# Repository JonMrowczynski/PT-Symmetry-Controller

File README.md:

# PT-Symmetry-Controller

PT-Symmetric Quantum Theory is a non-Hermitian area of physics whose study has relatively recently gained a significant amount of popularity. The interplay between energy additions and subtractions to and from a system can lead to features that present new and interesting research topics.

This mechanical PT-Symmetry-Controller project is an analog to a quantum mechanical PT-symmetric system. It consists of two pendulums that are energetically coupled by a string that connects their pivot points. The amount of energy that can be transferred between the pendulums is determined by the tautness of the coupling string.

One of these pendulums has energy added to its swing while the other pendulum has energy subtracted from its swing. This is done by pulsing the pendulum's corresponding solenoid at specific times such that a magnet, which is attached to the string of each pendulum, has a force exerted on it. The driven pendulum has its corresponding solenoid pulsed when it is swinging towards its solenoid, while the dampened pendulum has its corresponding solenoid pulsed when it is swinging away from its solenoid.

Each pendulum has a photogate that assists with determining its swing direction. Each photogate is placed slightly offset from the resting position of the corresponding pendulum. This allows for two asymmetrical partial periods to be determined. This information is then used by the computer to determine when to pulse the corresponding solenoid. The two photogates interface with a LabQuest 2, which needs to be connected to the computer that is running the program.

Finally, a custom circuit is used to help pulse the solenoids. The computer program communicates with a microcontroller using a USB to MIDI connection. Based on the MIDI message that is sent to the microcontroller, and with the help of high amperage transistors, current can be sent to and cut off from each corresponding solenoid.

With this equipment, one can setup either a broken (insufficient coupling), or an unbroken (sufficient coupling) PT-symmetric mechanical system.

## Requirements for...

### Electronics

- Any PDF reader to view the PDF of the schematic.

- [Autodesk Eagle](https://www.autodesk.com/products/eagle/free-download) >= 9.5 to modify the schematic, board layout, and/or Gerber files.

### Firmware

#### Software

- [MPLAB X IDE](https://www.microchip.com/mplab/mplab-x-ide) >= 5.25 to modify and develop the firmware.

- MPLAB X IPE >= 5.25 to program the PIC microcontrollers.

  - While installing the IDE, you are presented with the choice of also installed the IPE.
  
  - The versions of MPLAB X IDE and MPLAB X IPE should be the same.
  
#### Hardware

- [PICkit 4 In-Circuit Debugger/Programmer](https://www.microchip.com/developmenttools/ProductDetails/PG164140) to flash the PIC microcontrollers with new firmware.

### LabQuest 2 Software

- [Microsoft Visual Studio IDE](https://visualstudio.microsoft.com/) >= 2019

Using the Visual Studio Installer that comes with the IDE install the "Desktop development with C++" workload:
  
#### Hardware

- [LabQuest 2](https://www.vernier.com/products/interfaces/labq2/)

- 2 [Vernier Photogates](https://www.vernier.com/products/sensors/photogates/vpg-btd/)

### Master Control Software

#### Software

- Both [OpenJDK](https://adoptopenjdk.net/) and [OpenJFX](https://gluonhq.com/products/javafx/) >= 11 to run and develop the software.
  - The versions of OpenJDK and OpenJFX should be the same.
  
- [Intellij IDEA](https://www.jetbrains.com/idea/download/) >= 2019.2 (recommended, but not necessary).

#### Hardware 

- [USB to MIDI cable](https://www.amazon.com/HDE-Synthesizer-Microphone-Instrument-Converter/dp/B00D3QFHN8/)

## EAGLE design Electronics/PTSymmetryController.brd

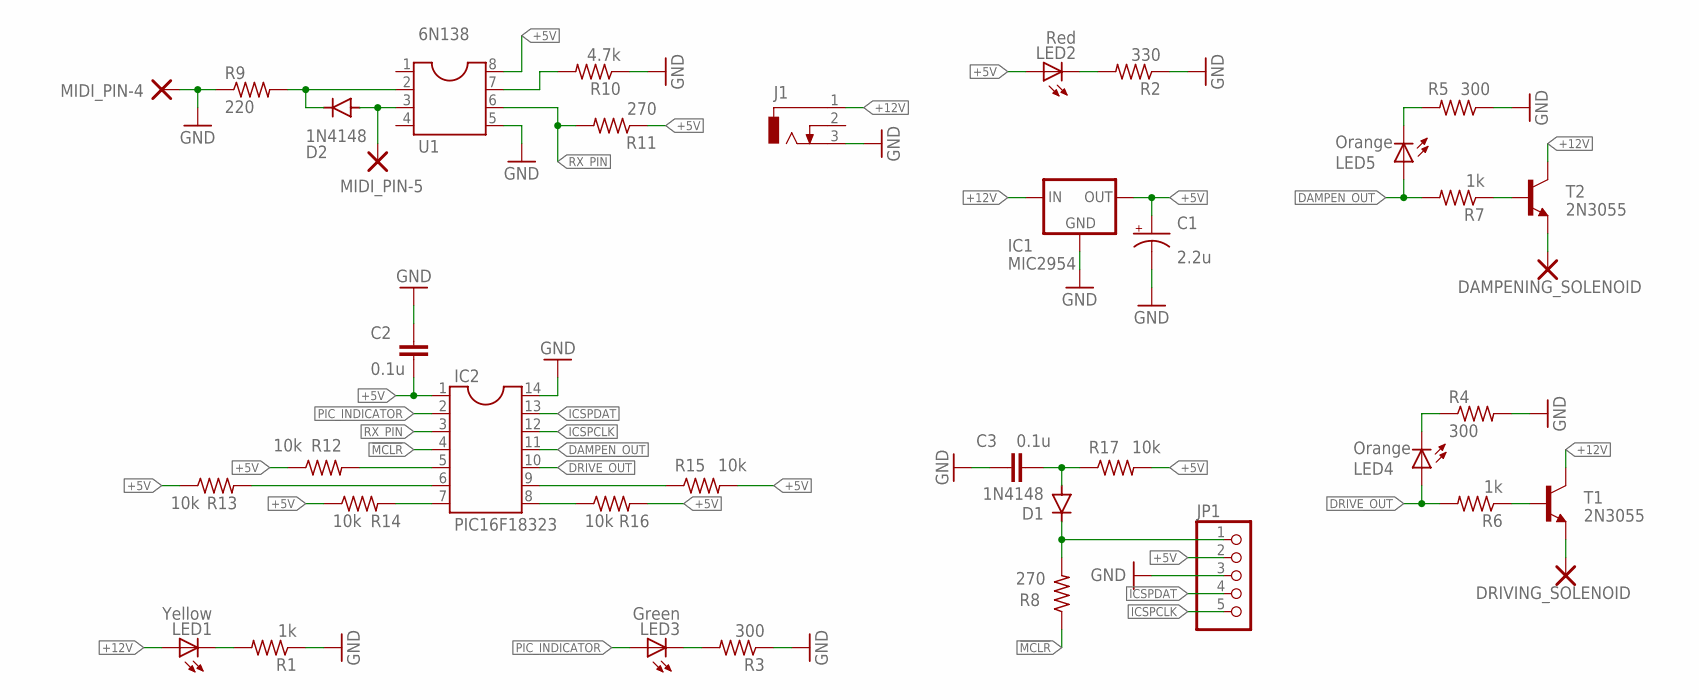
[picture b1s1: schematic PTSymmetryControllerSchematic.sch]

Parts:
6N138: U1; SOCKET-08
C1: 2.2u; E2,5-6
C2, C3: 0.1u; C5B2.5
D1, D2: 1N4148; DO35-10
DAMPENING_SOLENOID: DOUBLE_THROUGH_HOLE_PAD
DRIVING_SOLENOID: DOUBLE_THROUGH_HOLE_PAD
IC1: MIC2954; 78XXL
IC2: PIC16F18323; SOCKET-14
J1: DCJ0303
JP1: 1x5x2mm-pinheader; 1X05
LED1: Yellow; LED5MM
LED2: Red; LED5MM
LED3: Green; LED5MM
LED4, LED5: Orange; LED5MM
MIDI_PIN-4, MIDI_PIN-5: DOUBLE_THROUGH_HOLE_PAD
R1, R6, R7: 1k; 0207/10
R2: 330; 0207/10
R3, R4, R5: 300; 0207/10
R8: 270; 0207/10
R9: 220; 0207/12
R10: 4.7k; 0207/12
R11: 270; 0207/12
R12, R13, R14, R15, R16, R17: 10k; 0207/10
T1, T2: 2N3055; TO3

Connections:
!MCLR: IC2.4, R8.1
+5V: 6N138.8, C1.+, C2.2, IC1.OUT, IC2.1, JP1.2, LED2.A, R11.1, R12.1, R13.1, R14.1, R15.2, R16.2, R17.2
+12V: IC1.IN, J1.1, LED1.A, T1.C, T1.C/ (C), T2.C, T2.C/ (C)
DAMPEN_OUT: IC2.11, LED5.A, R7.2
DRIVE_OUT: IC2.10, LED4.A, R6.2
GND: 6N138.5, C1.-, C2.1, C3.1, IC1.GND, IC2.14, J1.3, JP1.3, MIDI_PIN-4.P$1, R1.1, R2.1, R3.1, R4.2, R5.1, R9.1, R10.1
ICSPCLK: IC2.12, JP1.5
ICSPDAT: IC2.13, JP1.4
MIDI_PIN-5: 6N138.3, D2.A, MIDI_PIN-5.P$1
unnamed: LED1.K (C), R1.2
unnamed: LED2.K (C), R2.2
unnamed: 6N138.7, R10.2
unnamed: LED5.K (C), R5.2
unnamed: LED4.K (C), R4.1
unnamed: C3.2, D1.A, R17.1
unnamed: D1.C, JP1.1, R8.2
unnamed: LED3.K (C), R3.2
unnamed: 6N138.2, D2.C, R9.2
unnamed: IC2.5, R12.2
unnamed: IC2.6, R13.2
unnamed: IC2.7, R14.2
unnamed: DRIVING_SOLENOID.P$1, T1.E
unnamed: IC2.9, R15.1
unnamed: R6.1, T1.B
unnamed: R7.1, T2.B
unnamed: IC2.8, R16.1
unnamed: DAMPENING_SOLENOID.P$1, T2.E
PIC_INDICATOR: IC2.2, LED3.A
RX_PIN: 6N138.6, IC2.3, R11.2

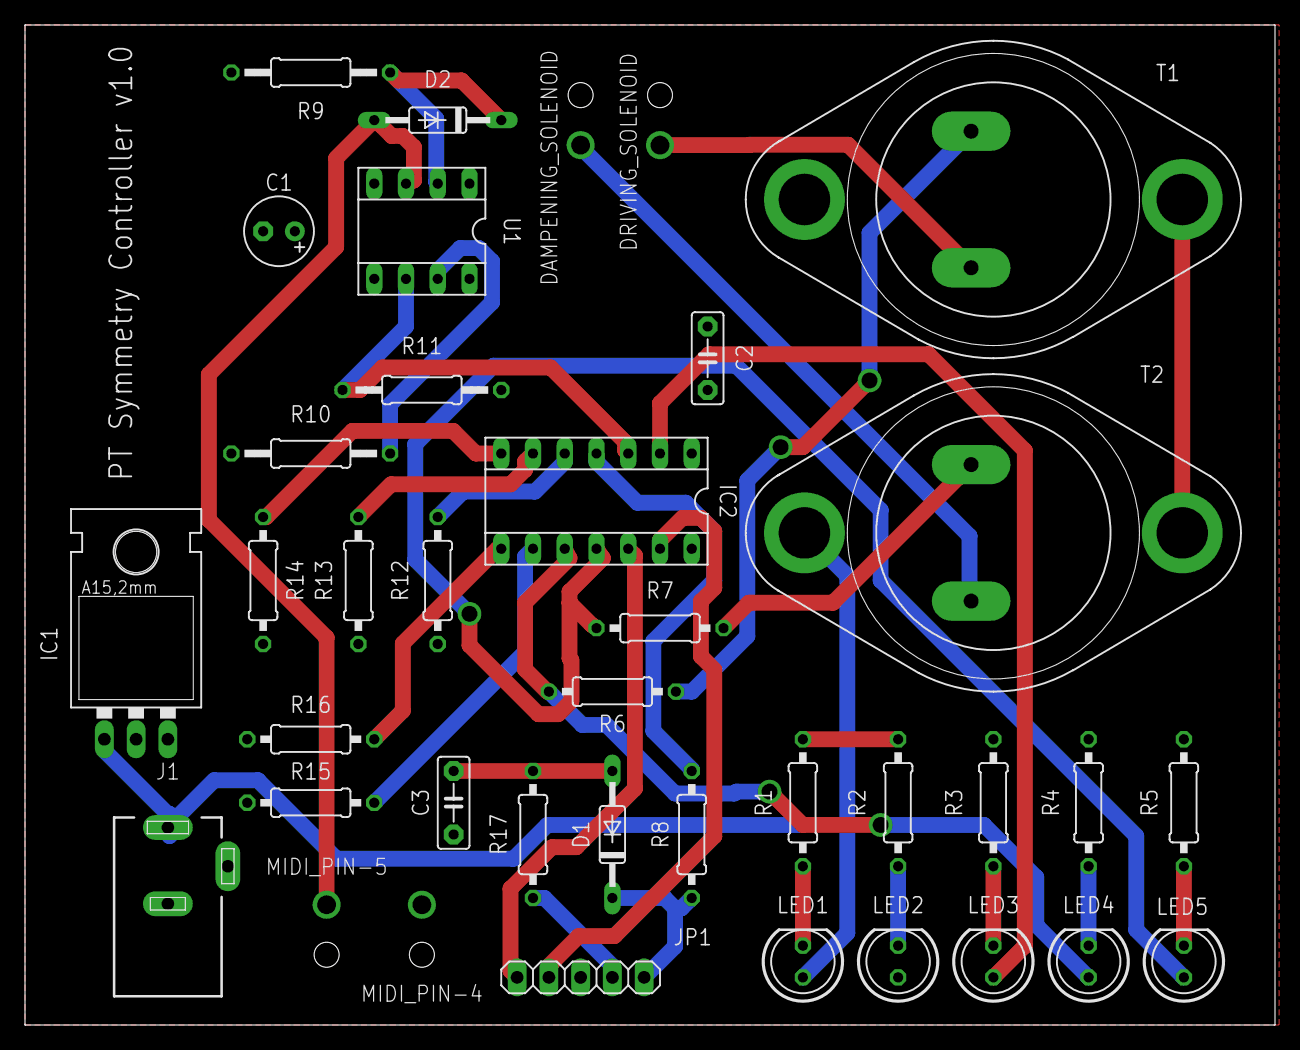
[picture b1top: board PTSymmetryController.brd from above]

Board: 2 copper layers, 100.0 x 80.0 mm, 38 parts (0 on the bottom side), 29 nets.

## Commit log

2018-08-30 Uploaded all original documents and code
2018-08-30 Revert "Uploaded all original documents and code"
    This reverts commit ca4568e30422c83c89430699d1bd38a9d541c643.
2018-08-30 Added all original code
2018-08-30 Fixed repository; All original documents should now be uploaded.
2018-08-31 Cleaned up the Java code
2018-08-31 Updated project dictionary
2018-08-31 Added index file
2018-08-31 Set theme jekyll-theme-cayman
2018-09-01 Updated workspace
2018-10-05 Condensed and cleaned classes
2018-10-16 Removed unneeded library file and updated schematic to include better LED indicators, ICSP, and more stable circuiry
2018-10-17 Made MPLAB project for firmware and updated photogate inputs in schematic
2018-10-17 Added built project
2018-10-17 Correctly named photogate tag
2018-10-23 Added "photogates" to circuit
2018-10-24 Updated Firmware based on changes made to electronics
2018-10-24 Got rid of LabQuest2 Software
2018-11-11 Added function and algorithm to help calculate the partial periods of the pendulums
2018-11-12 Finished implementing code to determine the partial periods of the pendulums
2018-11-12 Added some comments to bettre explain the PT-symmetry controller algorithm
2018-11-18 Added Serial communication functionality to Firmware
2018-11-18 Fixed untracked files
2018-11-18 Updated .gitignore
2018-11-18 Fixed newly untracked files
2019-06-10 Updated project vcs.
2019-09-15 Renamed USBMidiConnection class to better reflect Java class naming conventions.
2019-09-15 Got rid of non Intellij project.
2019-09-15 Made first cleaning pass through Java code.
2019-09-28 Added proper if-else logic in Solenoid class.
2019-09-28 Added LabQuest2 subproject.
2019-09-29 Got rid of unnecessary poritions of the NGIO_SDK
2019-09-29 Performed preliminary debugging of project.
2019-10-01 Restarted development of Firmware subproject to make it compatible with Software.
2019-10-01 Started cleaning up schematic and grouping subcircuits.
2019-10-01 Updated documentation.
2019-10-01 Cleaned up and finished debugging software.
2019-10-02 Finished schematic. Passed ERC.
2019-10-02 Finished board layout. Passed DRC.
2019-10-02 Saved CAM processor and produced Gerber files.
2019-10-09 Added datasheet for microcontroller.
2019-10-09 Got rid of old README file.
2019-10-09 Got rid of old .gitignore file and updated existing .gitignore files.
2019-10-10 Cleaned up code.
2019-10-10 Finished cleaning up code and comments.
2019-10-11 Created license file.
2019-10-11 Created README.md
2019-10-11 Added PDF and renamed schematic and board layout.
2019-10-11 Renamed PTSymmetryControllerSoftware to MasterControlSoftware.
2019-10-11 Removed old project file.
2019-10-11 Finished writing README.
2019-10-11 Fixed a few typos in README.
2019-10-11 Updated Java software project name in README
2019-10-12 Improved README lingo
